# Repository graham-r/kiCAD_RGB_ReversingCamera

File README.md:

# A&R A60 Amplifier KICAD projects

Version 8.01 differences

Compact style PCB
Power & speaker fuses removed
Common input socket (Left & Right)
+/-36v Power rails decoupled between power amp stage & input stage

NOTE: These are experiments in using KICAD - they are untested as they have not been built
(unless stated otherwise in the README file in a specific directory).

The projects contained in this repository are all based on the A&R A60 or A60AP integrated
amplifiers, currently limited to issue 8 (25502 onwards schematics).

The copyright of the circuits remain with the original owners, the Schematic and hardware
copyright are open source.

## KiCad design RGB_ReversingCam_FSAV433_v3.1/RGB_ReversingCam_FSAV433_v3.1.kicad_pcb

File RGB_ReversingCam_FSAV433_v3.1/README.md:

# Reversing camera interface for cars with an RGB  interface.

The projects in this repository have been tested (in Vero-board) prototype form for many
years on D2B equipped Jaguar X Type (X400) & S Type (X200) - will also work on the XJ (X350)

This module uses an FSAV433 video switch to switch between RGB & Sync (the default channel)
and an RGB & 'Sync-on-Green' camera input. The latter must be converted from cmposite to
RGB using a suitable video converter, in this case a 'Lindy' module was used.

This version uses an ATtiny85 Arduino style IC to control the reversing camera switching.

NOTE: These are experiments in using KICAD - they are untested as they have not been built
(unless stated otherwise in the README file in a specific directory).

The projects contained in this repository are all based on the A&R A60 or A60AP integrated
amplifiers, currently limited to issue 8 (25502 onwards schematics).

The copyright of the circuits remain with the original owners, the Schematic and hardware
copyright are open source.

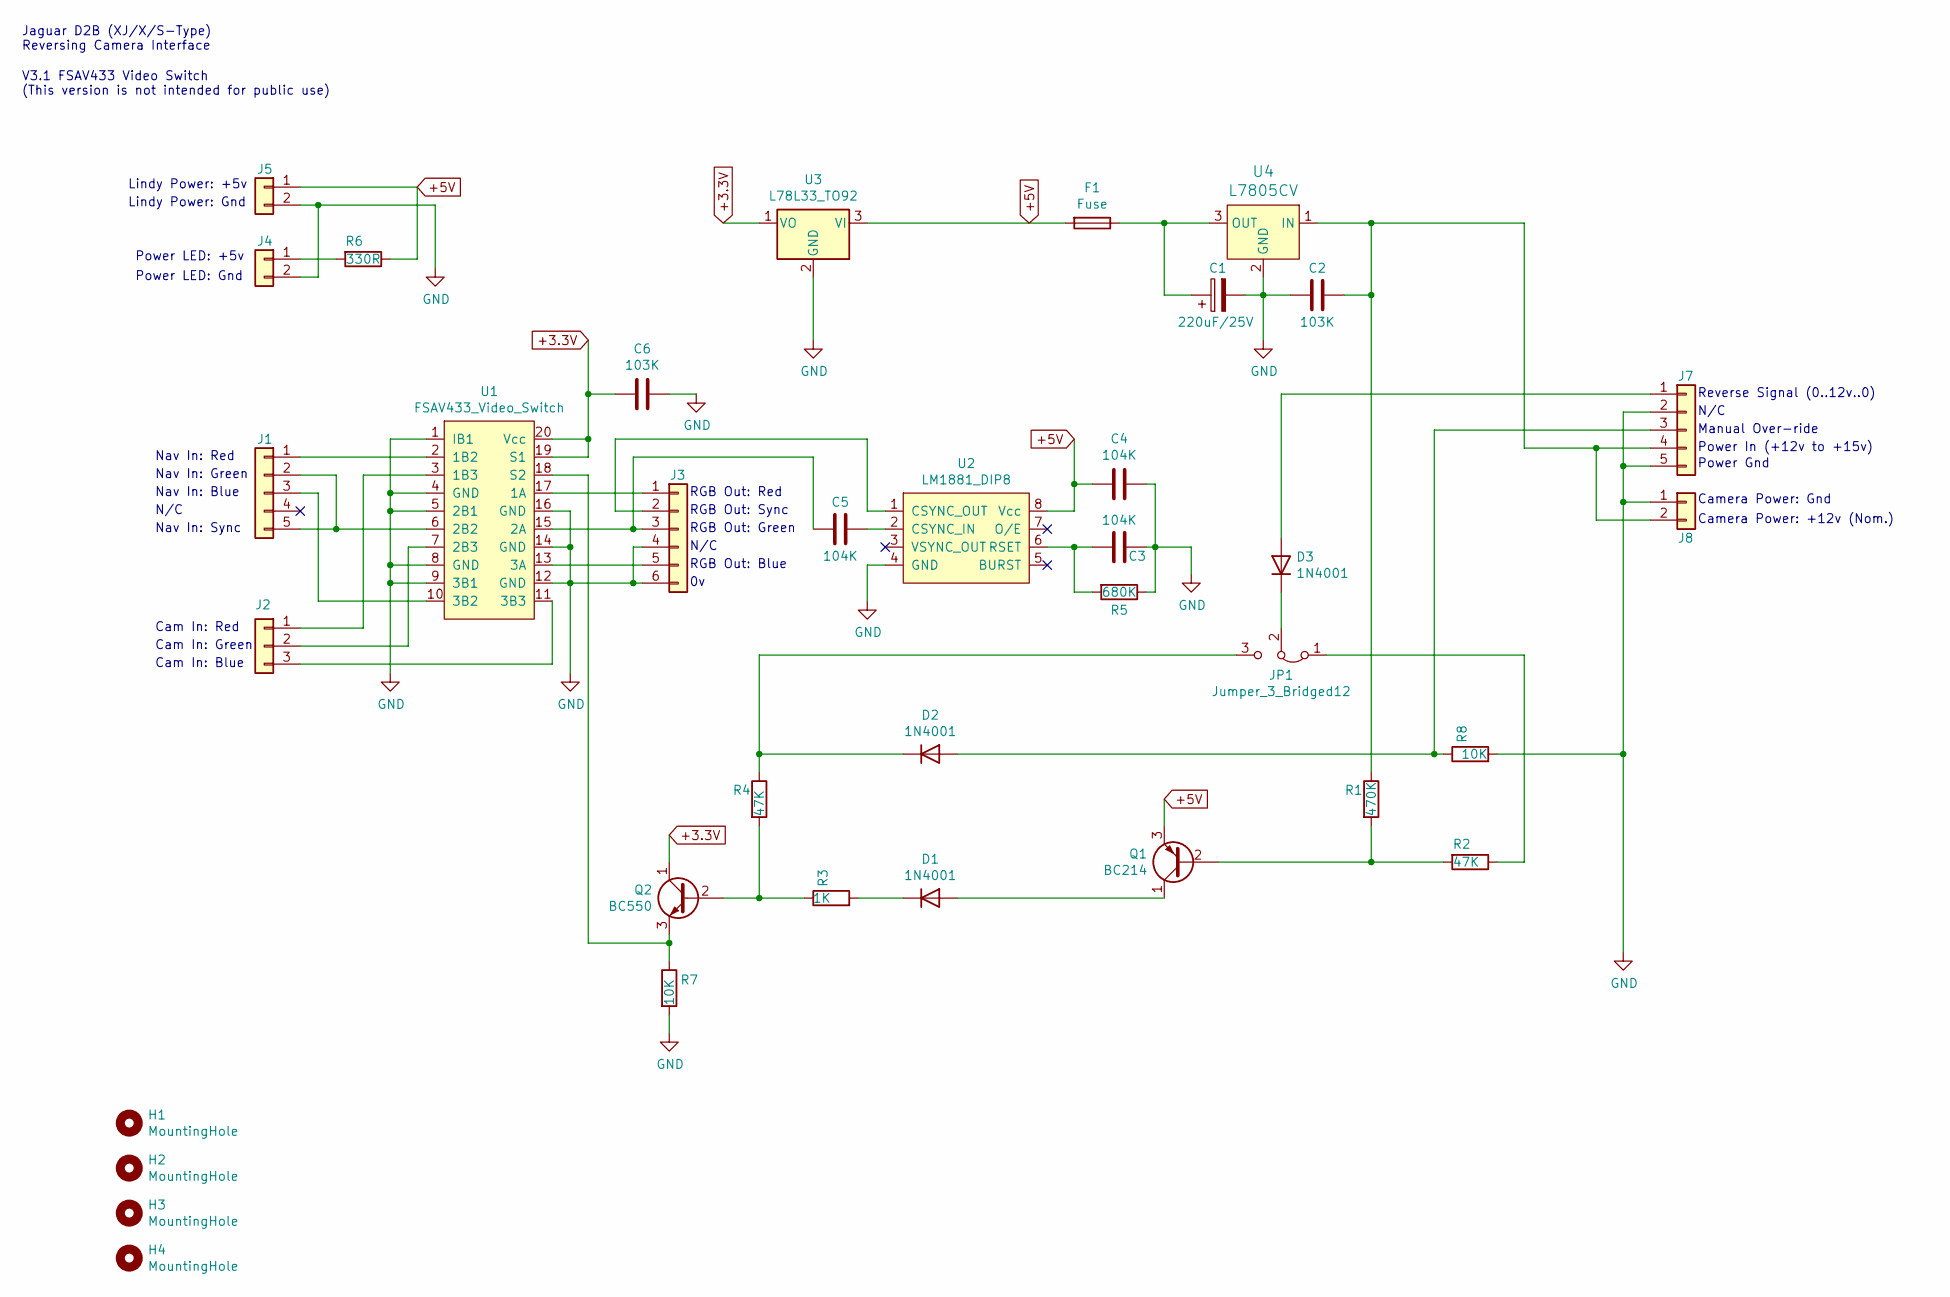
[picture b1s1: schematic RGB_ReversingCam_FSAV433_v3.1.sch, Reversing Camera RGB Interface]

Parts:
C1: 220uF/25V; CP_Radial_D8.0mm_P2.50mm
C2, C6: 103K; C_Rect_L7.0mm_W2.5mm_P5.00mm
C3, C4, C5: 104K; C_Rect_L7.0mm_W2.5mm_P5.00mm
D1, D2, D3: 1N4001; D_DO-41_SOD81_P10.16mm_Horizontal
F1: Fuse; Fuseholder_Cylinder-5x20mm_Stelvio-Kontek_PTF78_Horizontal_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
H1, H2, H3: MountingHole; MountingHole_3.2mm_M3_ISO7380
H4: MountingHole; MountingHole_3.2mm_M3_ISO7380_no_courtyard
J1: Conn_01x05; Molex_KK-254_AE-6410-05A_1x05_P2.54mm_Vertical
J2: Conn_01x03; Molex_KK-254_AE-6410-03A_1x03_P2.54mm_Vertical
J3: Conn_01x06; Molex_KK-254_AE-6410-06A_1x06_P2.54mm_Vertical
J4, J5: Conn_01x03; JST_XH_B2B-XH-A_1x02_P2.50mm_Vertical
J7: Conn_01x05; JST_XH_B5B-XH-A_1x05_P2.50mm_Vertical
J8: Conn_01x02; JST_XH_B2B-XH-A_1x02_P2.50mm_Vertical
JP1: Jumper_3_Bridged12; PinHeader_1x03_P2.54mm_Vertical
Q1: BC214; TO-92_Inline
Q2: BC550; TO-92_Inline
R1: 470K; R_Axial_DIN0309_L9.0mm_D3.2mm_P12.70mm_Horizontal
R2, R4: 47K; R_Axial_DIN0309_L9.0mm_D3.2mm_P12.70mm_Horizontal
R3: 1K; R_Axial_DIN0309_L9.0mm_D3.2mm_P12.70mm_Horizontal
R5: 680K; R_Axial_DIN0309_L9.0mm_D3.2mm_P12.70mm_Horizontal
R6: 330R; R_Axial_DIN0309_L9.0mm_D3.2mm_P12.70mm_Horizontal
R7, R8: 10K; R_Axial_DIN0309_L9.0mm_D3.2mm_P12.70mm_Horizontal
U1: FSAV433_Video_Switch; TSSOP-20_W4.4mm
U2: LM1881_DIP8; DIP-8_W7.62mm_Socket
U3: L78L33_TO92; TO-92_Inline
U4: L7805CV; TO-220-3; MPN L7805CV; Digi-Key_PN 497-1443-5-ND

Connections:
+3.3V: C6.1, Q2.1 (C), U1.19 (S1), U1.20 (Vcc), U3.1 (VO)
+5V: C4.2, F1.2, J5.1, Q1.3 (E), R6.1, U2.8 (Vcc), U3.3 (VI)
GND: C1.2, C2.1, C3.1, C4.1, C6.2, J3.4, J3.6, J4.2, J5.2, J7.2, J7.5, J8.1, R5.1, R7.2, R8.2, U1.1 (IB1), U1.4 (GND), U1.5 (2B1), U1.8 (GND), U1.9 (3B1), U1.12 (GND), U1.14 (GND), U1.16 (GND), U2.4 (GND), U3.2 (GND), U4.2 (GND)
unnamed: C1.1, F1.1, U4.3 (OUT)
unnamed: C2.2, J7.4, J8.2, R1.1, U4.1 (IN)
unnamed: C3.2, R5.2, U2.6 (RSET)
unnamed: C5.1, U2.2 (CSYNC_IN)
unnamed: C5.2, J3.3, U1.15 (2A)
unnamed: D1.1 (K), R3.2
unnamed: D1.2 (A), Q1.1 (C)
unnamed: D2.1 (K), JP1.3 (B), R4.1
unnamed: D2.2 (A), J7.3, R8.1
unnamed: D3.1 (K), JP1.2 (C)
unnamed: D3.2 (A), J7.1
unnamed: J1.1, U1.2 (1B2)
unnamed: J1.2, J1.5, U1.6 (2B2)
unnamed: J1.3, U1.10 (3B2)
unnamed: J2.1, U1.3 (1B3)
unnamed: J2.2, U1.7 (2B3)
unnamed: J2.3, U1.11 (3B3)
unnamed: J3.1, U1.17 (1A)
unnamed: J3.2, U2.1 (CSYNC_OUT)
unnamed: J3.5, U1.13 (3A)
unnamed: J4.1, R6.2
unnamed: JP1.1 (A), R2.1
unnamed: Q1.2 (B), R1.2, R2.2
unnamed: Q2.2 (B), R3.1, R4.2
unnamed: Q2.3 (E), R7.1, U1.18 (S2)

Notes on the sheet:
RGB Out: Blue
N/C
RGB Out: Green
RGB Out: Sync
RGB Out: Red
Cam In: Blue
Cam In: Green
Cam In: Red
Nav In: Sync
Nav In: Blue
Nav In: Green
Nav In: Red
Reverse Signal (0..12v..0)
Manual Over-ride
Power In (+12v to +15v)
Power Gnd
Camera Power: Gnd
Camera Power: +12v (Nom.)
Jaguar D2B (XJ/X/S-Type) Reversing Camera Interface
V3.1 FSAV433 Video Switch (This version is not intended for public use)
Lindy Power: +5v
Lindy Power: Gnd
Power LED: Gnd
Power LED: +5v

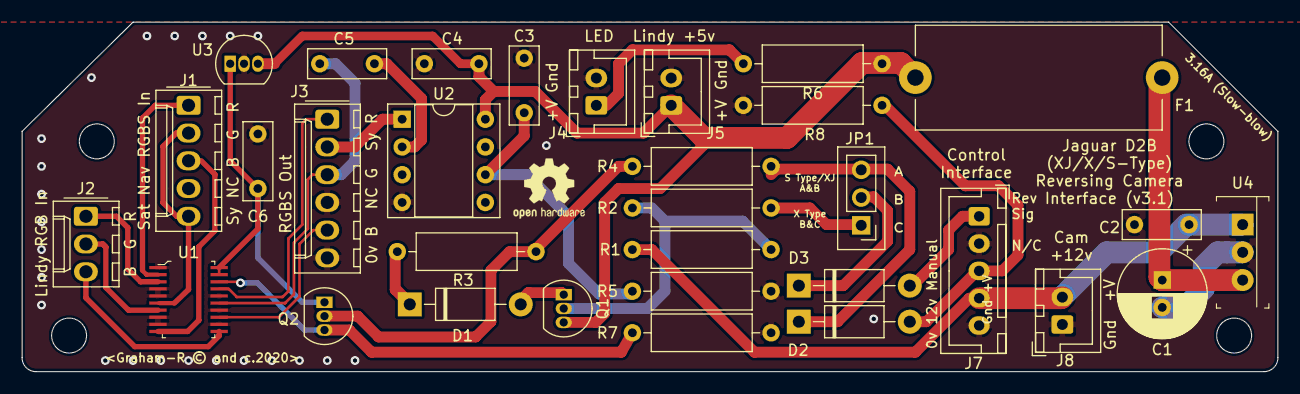
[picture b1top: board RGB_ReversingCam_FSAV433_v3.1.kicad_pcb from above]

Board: 2 copper layers, 115.0 x 32.0 mm, 36 parts (0 on the bottom side), 28 nets.

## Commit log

2020-04-28 Initial commit for Reversing Camera
